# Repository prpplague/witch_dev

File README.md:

WITCH Development
=========

Repository for misc documents and code relating to the study of the Harwell
WITCH. The Harwell computer, later known as the Wolverhampton Instrument for
Teaching Computing from Harwell (WITCH), or the Harwell Dekatron Computer,
was an early British relay-based computer. It is currently being restored at
The National Museum of Computing at Bletchley Park, where it is described as
"the oldest original functioning electronic stored program computer in the 
world".

http://www.witch-e.org

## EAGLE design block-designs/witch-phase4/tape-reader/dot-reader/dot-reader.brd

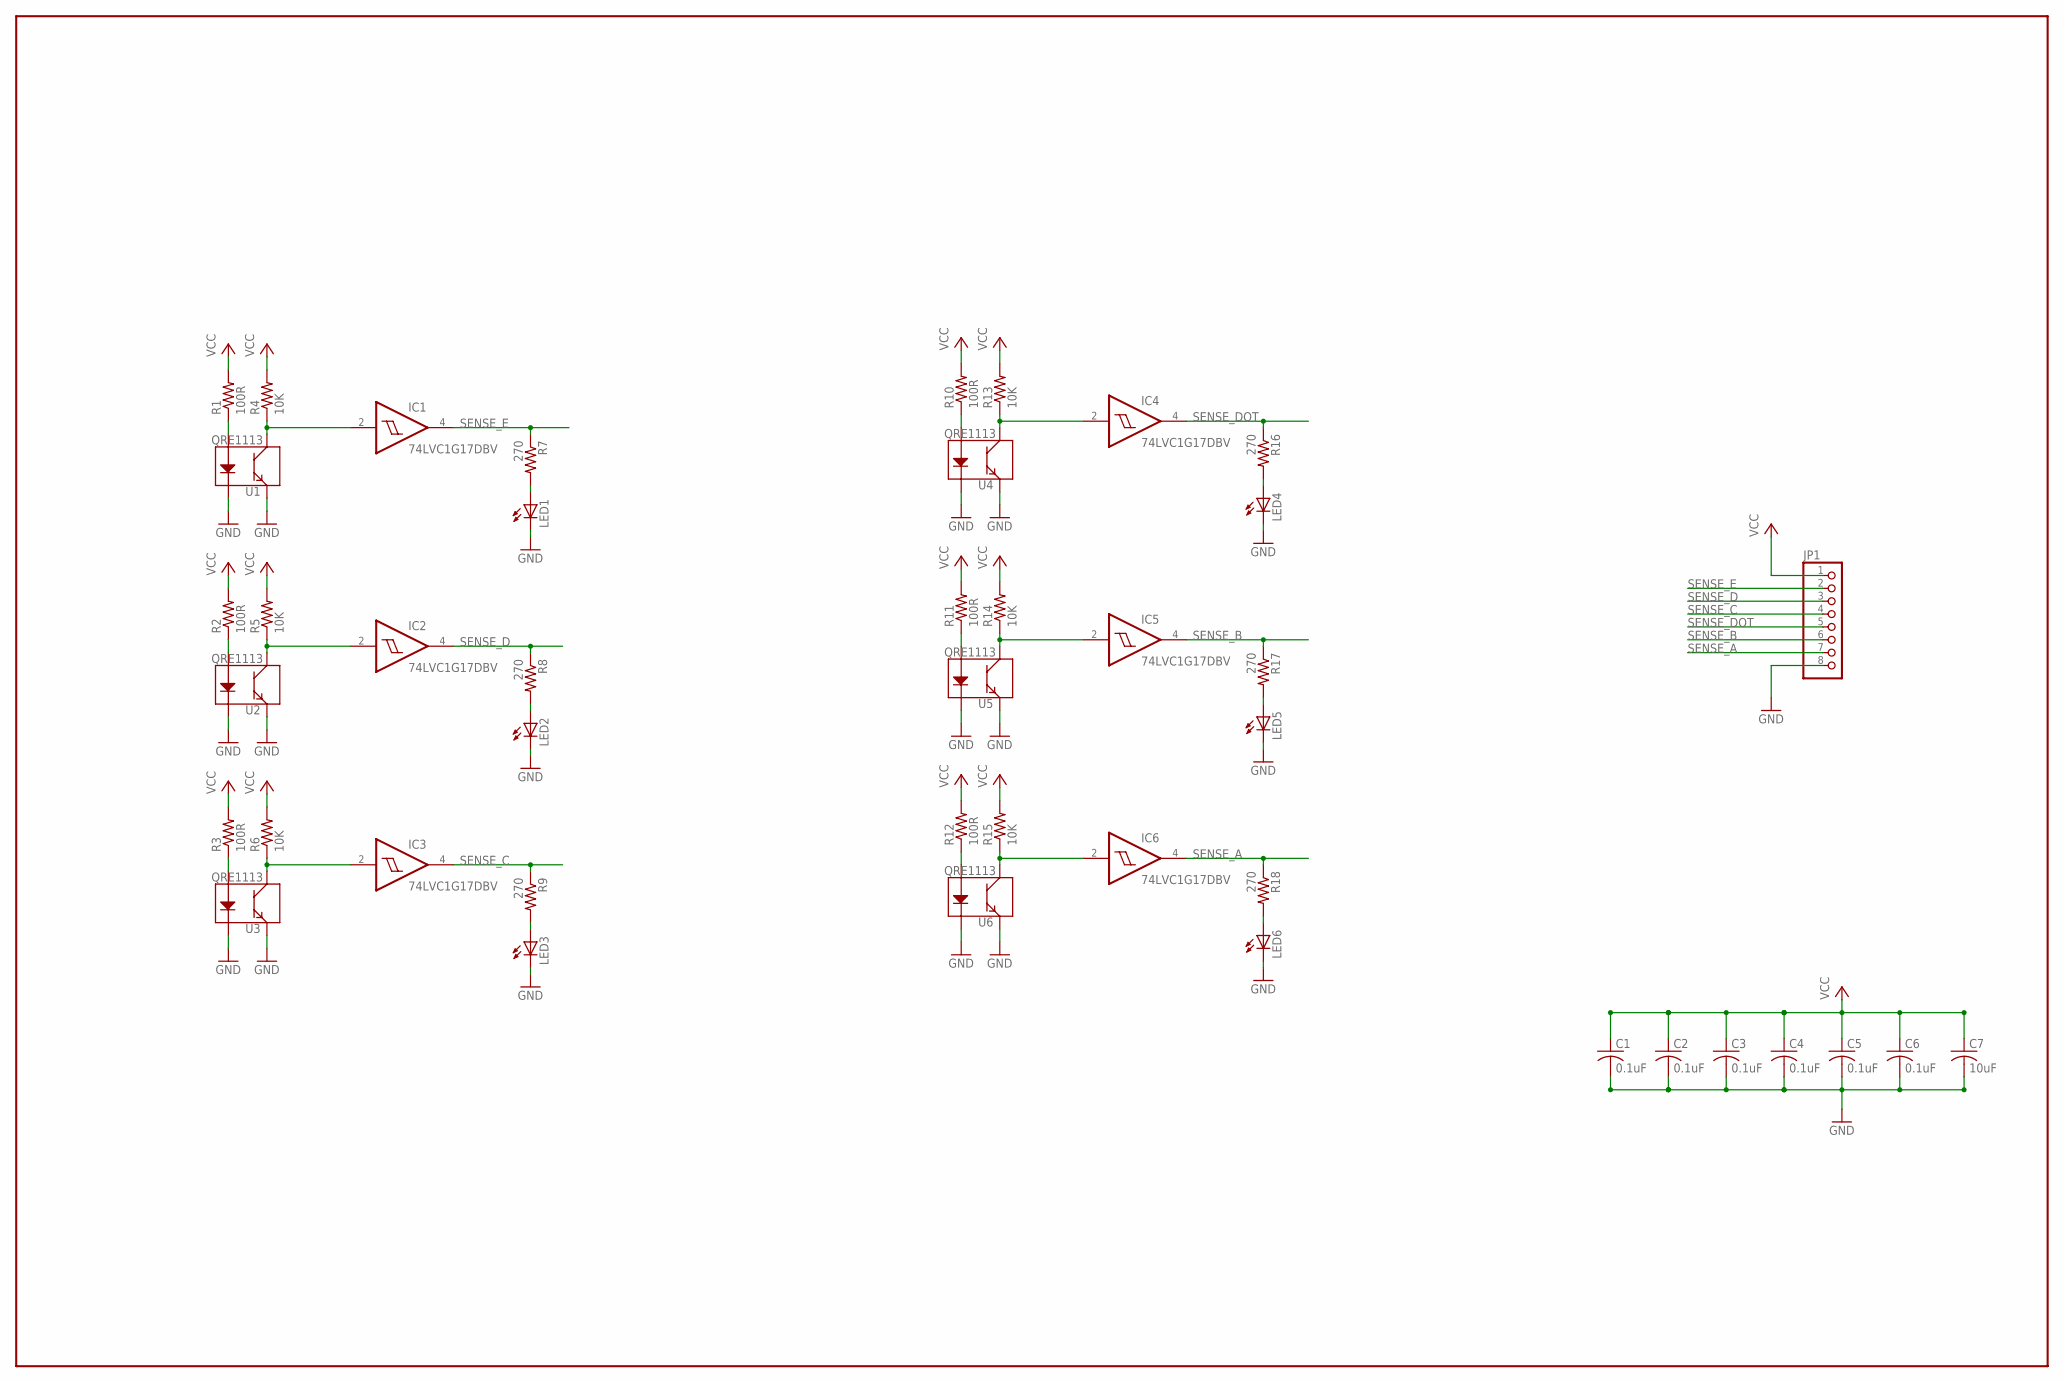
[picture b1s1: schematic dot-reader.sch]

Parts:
C1, C2, C3, C4, C5, C6: 0.1uF; C0603
C7: 10uF; C0805
IC1, IC2, IC3, IC4, IC5, IC6: 74LVC1G17DBV; SOT23-5
JP1: PINHD-1X8; 1X08
LED1, LED2, LED3, LED4, LED5, LED6: LEDCHIP-LED0805; CHIP-LED0805
R1, R2, R3, R10, R11, R12: 100R; M0805
R4, R5, R6, R13, R14, R15: 10K; M0805
R7, R8, R9, R16, R17, R18: 270; R0805
U1, U2, U3, U4, U5, U6: QRE1113

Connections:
A: IC1.2 (I), R4.1, U1.3 (C)
B: IC2.2 (I), R5.1, U2.3 (C)
C: IC4.2 (I), R13.1, U4.3 (C)
D: IC5.2 (I), R14.1, U5.3 (C)
DOT: IC3.2 (I), R6.1, U3.3 (C)
E: IC6.2 (I), R15.1, U6.3 (C)
GND: C1.2, C2.2, C3.2, C4.2, C5.2, C6.2, C7.2, IC1.3 (GND), IC2.3 (GND), IC3.3 (GND), IC4.3 (GND), IC5.3 (GND), IC6.3 (GND), JP1.8, LED1.C, LED2.C, LED3.C, LED4.C, LED5.C, LED6.C, U1.2 (K), U1.4 (E), U2.2 (K), U2.4 (E), U3.2 (K), U3.4 (E), U4.2 (K), U4.4 (E), U5.2 (K), U5.4 (E), U6.2 (K), U6.4 (E)
unnamed: R1.1, U1.1 (A)
unnamed: LED2.A, R8.2
unnamed: R2.1, U2.1 (A)
unnamed: LED4.A, R16.2
unnamed: R3.1, U3.1 (A)
unnamed: LED5.A, R17.2
unnamed: R10.1, U4.1 (A)
unnamed: LED3.A, R9.2
unnamed: R11.1, U5.1 (A)
unnamed: LED6.A, R18.2
unnamed: R12.1, U6.1 (A)
unnamed: LED1.A, R7.2
SENSE_A: IC6.4 (O), JP1.7, R18.1
SENSE_B: IC5.4 (O), JP1.6, R17.1
SENSE_C: IC3.4 (O), JP1.4, R9.1
SENSE_D: IC2.4 (O), JP1.3, R8.1
SENSE_DOT: IC4.4 (O), JP1.5, R16.1
SENSE_E: IC1.4 (O), JP1.2, R7.1
VCC: C1.1, C2.1, C3.1, C4.1, C5.1, C6.1, C7.1, IC1.5 (VCC), IC2.5 (VCC), IC3.5 (VCC), IC4.5 (VCC), IC5.5 (VCC), IC6.5 (VCC), JP1.1, R1.2, R2.2, R3.2, R4.2, R5.2, R6.2, R10.2, R11.2, R12.2, R13.2, R14.2, R15.2

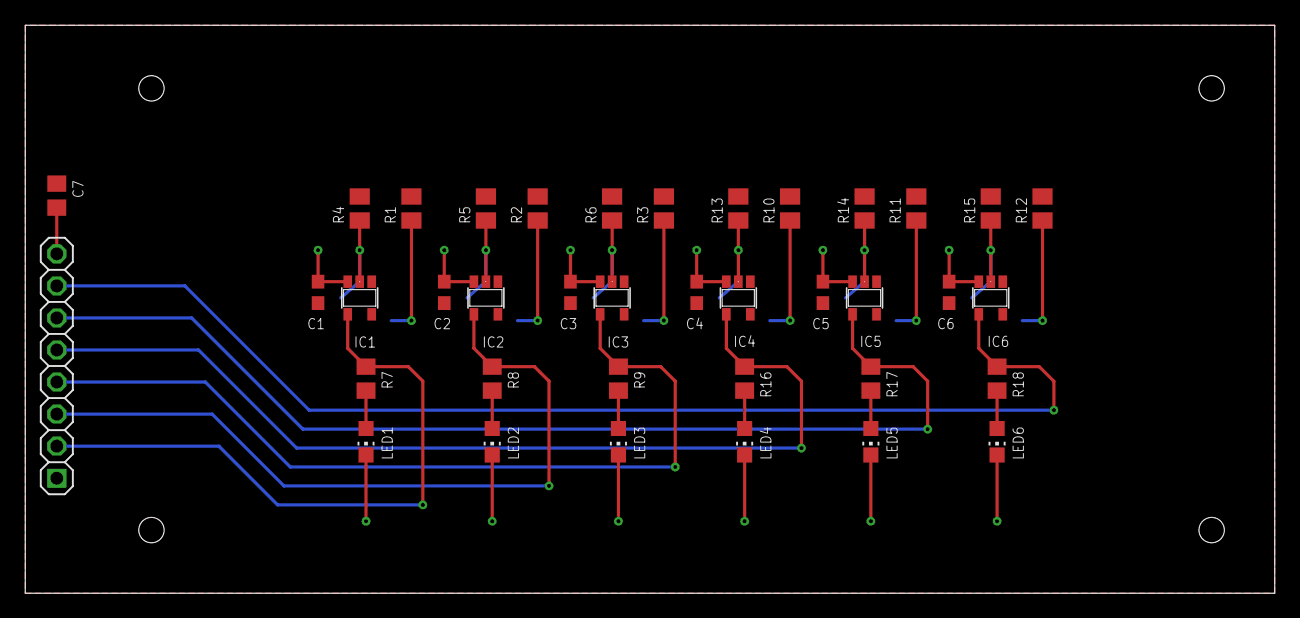
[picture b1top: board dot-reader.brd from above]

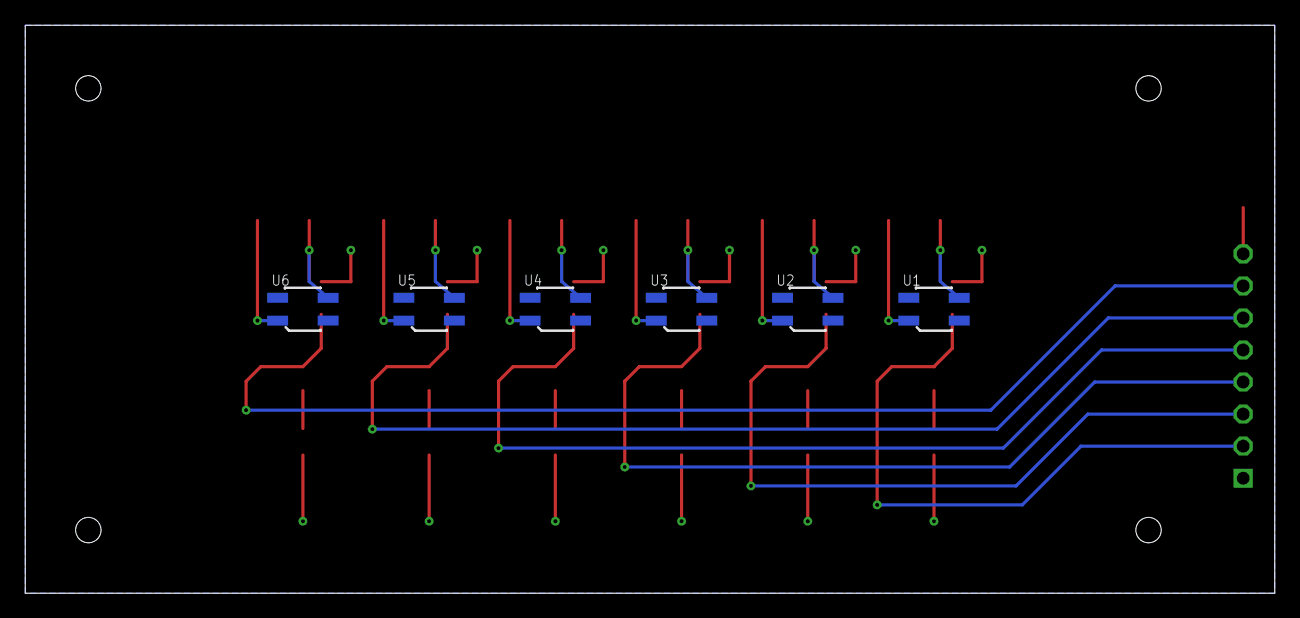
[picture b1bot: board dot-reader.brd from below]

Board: 2 copper layers, 99.0 x 45.0 mm, 44 parts (6 on the bottom side), 26 nets.

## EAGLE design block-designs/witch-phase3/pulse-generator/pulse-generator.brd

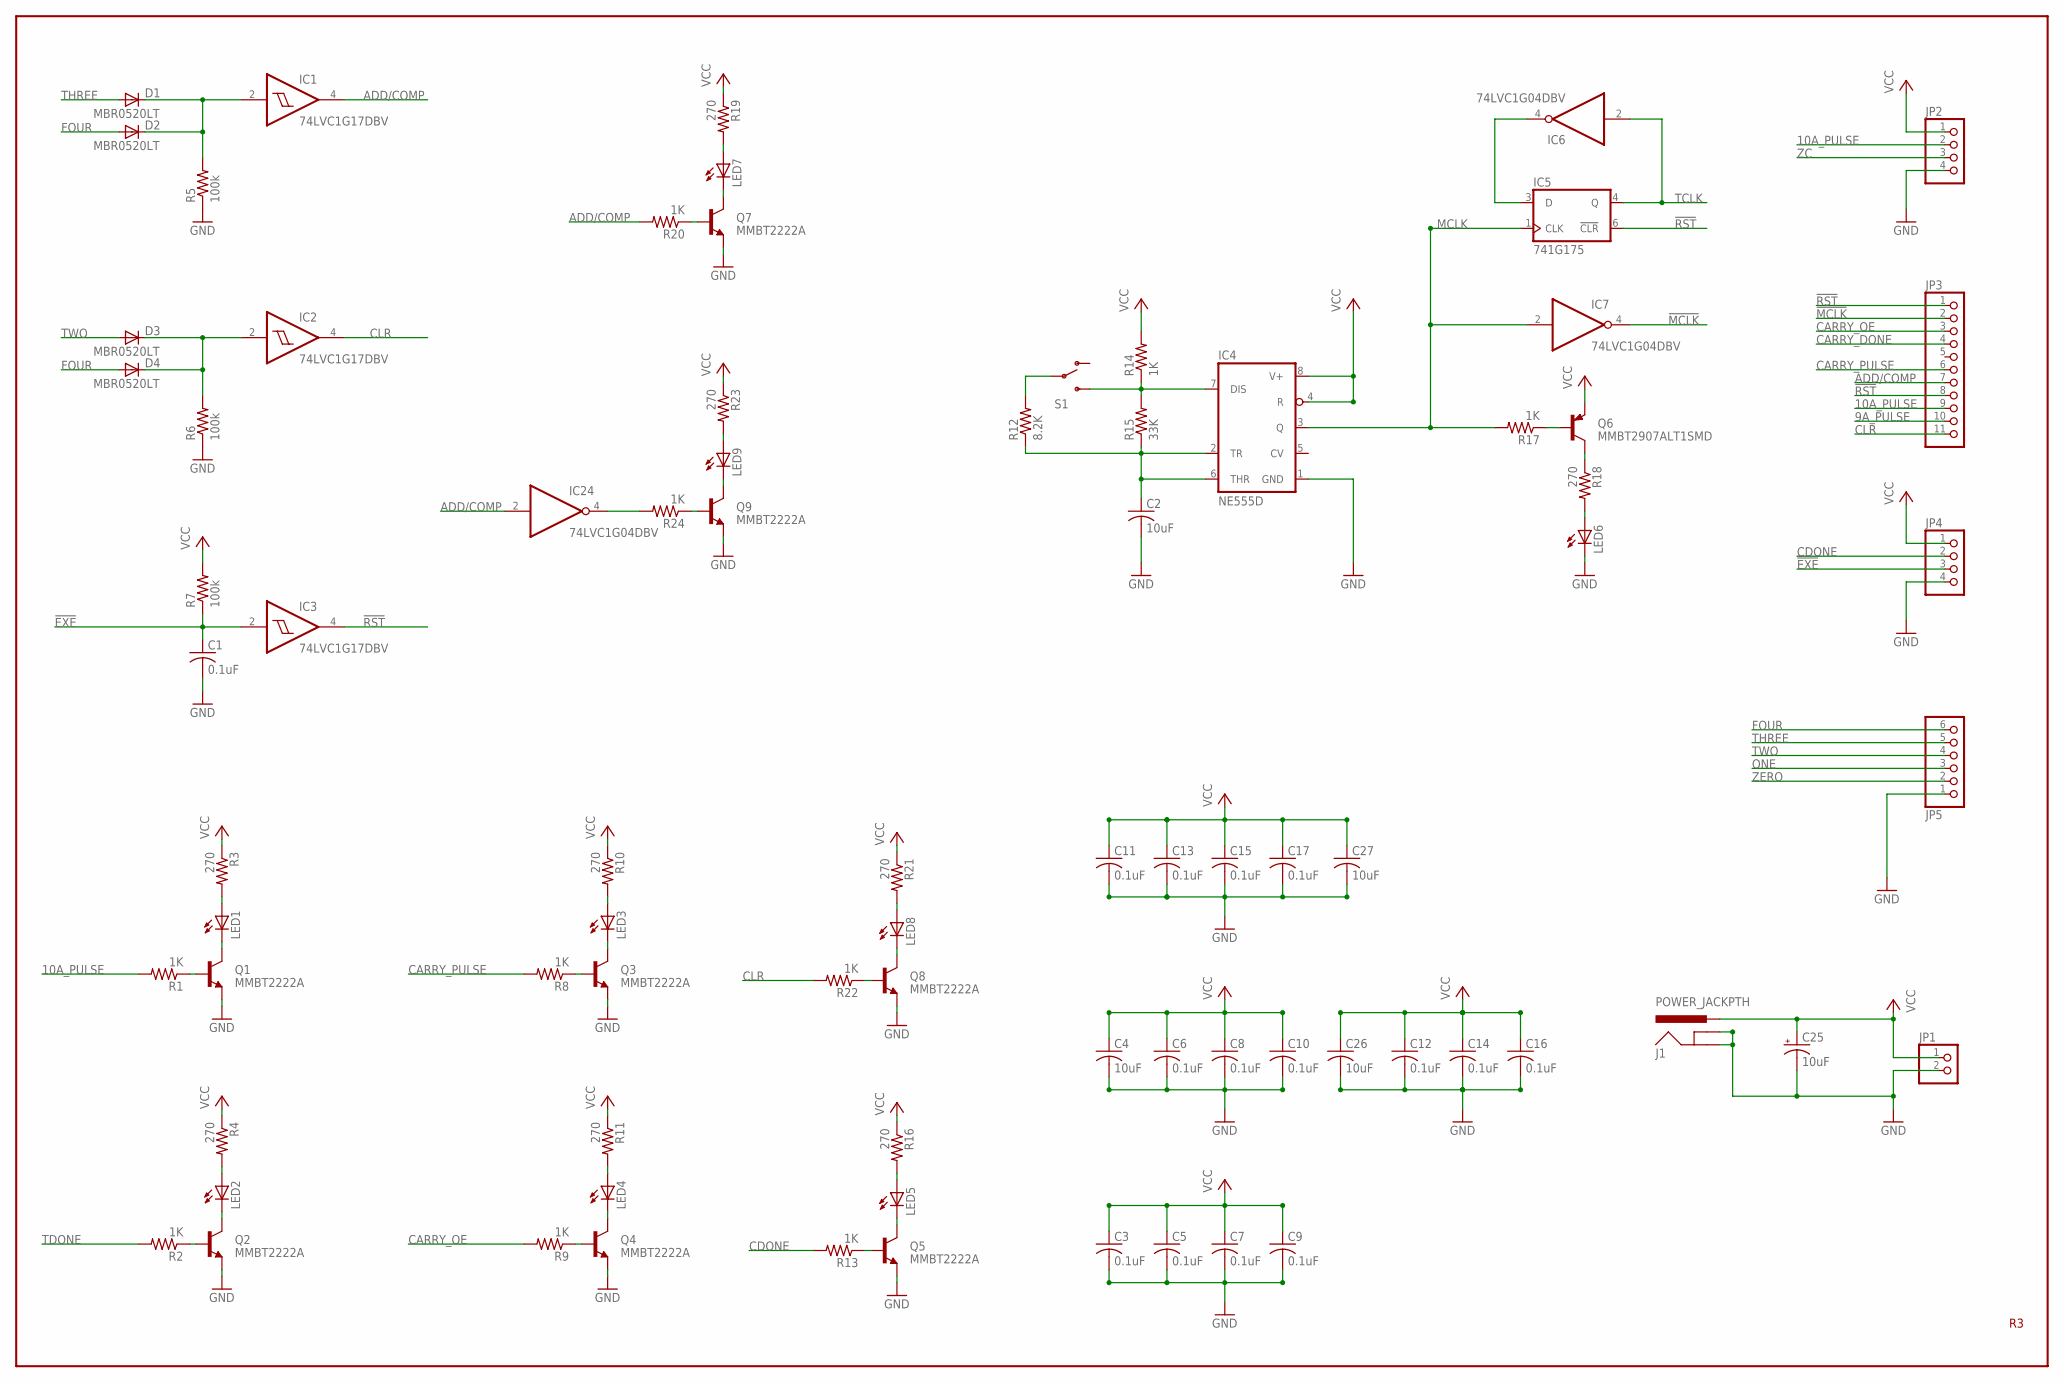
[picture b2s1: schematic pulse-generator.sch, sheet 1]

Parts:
C1, C7: 0.1uF; C0805
C2, C4, C26, C27: 10uF; C0805
C3, C5, C6, C8, C9, C10, C11, C12, C13, C14, C15, C16, C17: 0.1uF; C0603
C25: 10uF; EIA3216
D1, D2, D3, D4: MBR0520LT; SOD123
IC1, IC2, IC3: 74LVC1G17DBV; SOT23-5
IC4: NE555D; SO08
IC5: 741G175; DBV_R-PDSO-G6
IC6, IC7, IC24: 74LVC1G04DBV; SOT23-5
J1: POWER_JACKPTH; POWER_JACK_PTH
JP1: PINHD-1X2; 1X02
JP2, JP4: PINHD-1X4; 1X04
JP3: PINHD-1X11; 1X11
JP5: PINHD-1X6; 1X06
LED1, LED2, LED3, LED4, LED5, LED6, LED7, LED8, LED9: LEDCHIP-LED0805; CHIP-LED0805
Q1, Q2, Q3, Q4, Q5, Q7, Q8, Q9: MMBT2222A; SOT23-3
Q6: MMBT2907ALT1SMD; SOT23-BEC
R1, R2, R8, R9, R13, R14, R17, R20, R22, R24: 1K; R0805
R3, R4, R10, R11, R16, R18, R19, R21, R23: 270; R0805
R5, R6, R7: 100k; R0805
R12: 8.2K; R0805
R15: 33K; R0805
S1: SWITCH-SPDTPTH; SWITCH-SPDT

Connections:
9A_PULSE: JP3.10; also elsewhere on the board
10A_PULSE: JP2.2, JP3.9, R1.2; also elsewhere on the board
!EXE: C1.1, IC3.2 (I), JP4.3, R7.1
!MCLK: IC7.4 (O), JP3.2; also elsewhere on the board
!RST: IC3.4 (O), IC5.6 (!CLR), JP3.1, JP3.8; also elsewhere on the board
ADD/COMP: IC1.4 (O), IC24.2 (I), JP3.7, R20.2
CARRY_DONE: JP3.4; also elsewhere on the board
CARRY_OE: JP3.3, R9.2; also elsewhere on the board
CARRY_PULSE: JP3.6, R8.2; also elsewhere on the board
CDONE: JP4.2, R13.2; also elsewhere on the board
CLR: IC2.4 (O), JP3.11, R22.2
FOUR: D2.A, D4.A, JP5.6
GND: C1.2, C2.2, C3.2, C4.2, C5.2, C6.2, C7.2, C8.2, C9.2, C10.2, C11.2, C12.2, C13.2, C14.2, C15.2, C16.2, C17.2, C25.C (-), C26.2, C27.2, IC1.3 (GND), IC2.3 (GND), IC3.3 (GND), IC4.1 (GND), IC5.2 (GND), IC6.3 (GND), IC7.3 (GND), IC24.3 (GND), J1.GND, J1.GNDBREAK, JP1.2, JP2.4, JP4.4, JP5.1, LED6.C, Q1.2 (E), Q2.2 (E), Q3.2 (E), Q4.2 (E), Q5.2 (E), Q7.2 (E), Q8.2 (E), Q9.2 (E), R5.1, R6.1; also elsewhere on the board
MCLK: IC4.3 (Q), IC5.1 (CLK), IC7.2 (I), R17.2
unnamed: IC5.3 (D), IC6.4 (O)
unnamed: C2.1, IC4.2 (TR), IC4.6 (THR), R12.1, R15.1
unnamed: IC4.7 (DIS), R14.1, R15.2, S1.3 (S)
unnamed: R12.2, S1.2
unnamed: Q6.B, R17.1
unnamed: Q6.C, R18.1
unnamed: LED6.A, R18.2
unnamed: LED3.C, Q3.3 (C)
unnamed: LED7.C, Q7.3 (C)
unnamed: LED1.C, Q1.3 (C)
unnamed: Q7.1 (B), R20.1
unnamed: D1.C, D2.C, IC1.2 (I), R5.2
unnamed: D3.C, D4.C, IC2.2 (I), R6.2
unnamed: LED7.A, R19.2
unnamed: LED8.C, Q8.3 (C)
unnamed: Q8.1 (B), R22.1
unnamed: Q3.1 (B), R8.1
unnamed: LED3.A, R10.2
unnamed: Q1.1 (B), R1.1
unnamed: LED8.A, R21.2
unnamed: LED1.A, R3.2
unnamed: LED9.C, Q9.3 (C)
unnamed: Q9.1 (B), R24.1
unnamed: LED2.C, Q2.3 (C)
unnamed: Q2.1 (B), R2.1
unnamed: LED2.A, R4.2
unnamed: LED4.C, Q4.3 (C)
unnamed: Q4.1 (B), R9.1
unnamed: LED4.A, R11.2
unnamed: LED5.C, Q5.3 (C)
unnamed: Q5.1 (B), R13.1
unnamed: LED5.A, R16.2
unnamed: LED9.A, R23.2
unnamed: IC24.4 (O), R24.2
ONE: JP5.3
TCLK: IC5.4 (Q), IC6.2 (I); also elsewhere on the board
TDONE: R2.2; also elsewhere on the board
THREE: D1.A, JP5.5
TWO: D3.A, JP5.4
VCC: C3.1, C4.1, C5.1, C6.1, C7.1, C8.1, C9.1, C10.1, C11.1, C12.1, C13.1, C14.1, C15.1, C16.1, C17.1, C25.A (+), C26.1, C27.1, IC1.5 (VCC), IC2.5 (VCC), IC3.5 (VCC), IC4.4 (R), IC4.8 (V+), IC5.5 (VCC), IC6.5 (VCC), IC7.5 (VCC), IC24.5 (VCC), J1.PWR, JP1.1, JP2.1, JP4.1, Q6.E, R3.1, R4.1, R7.2, R10.1, R11.1, R14.2, R16.1, R19.1, R21.1, R23.1; also elsewhere on the board
ZC: JP2.3; also elsewhere on the board
ZERO: JP5.2

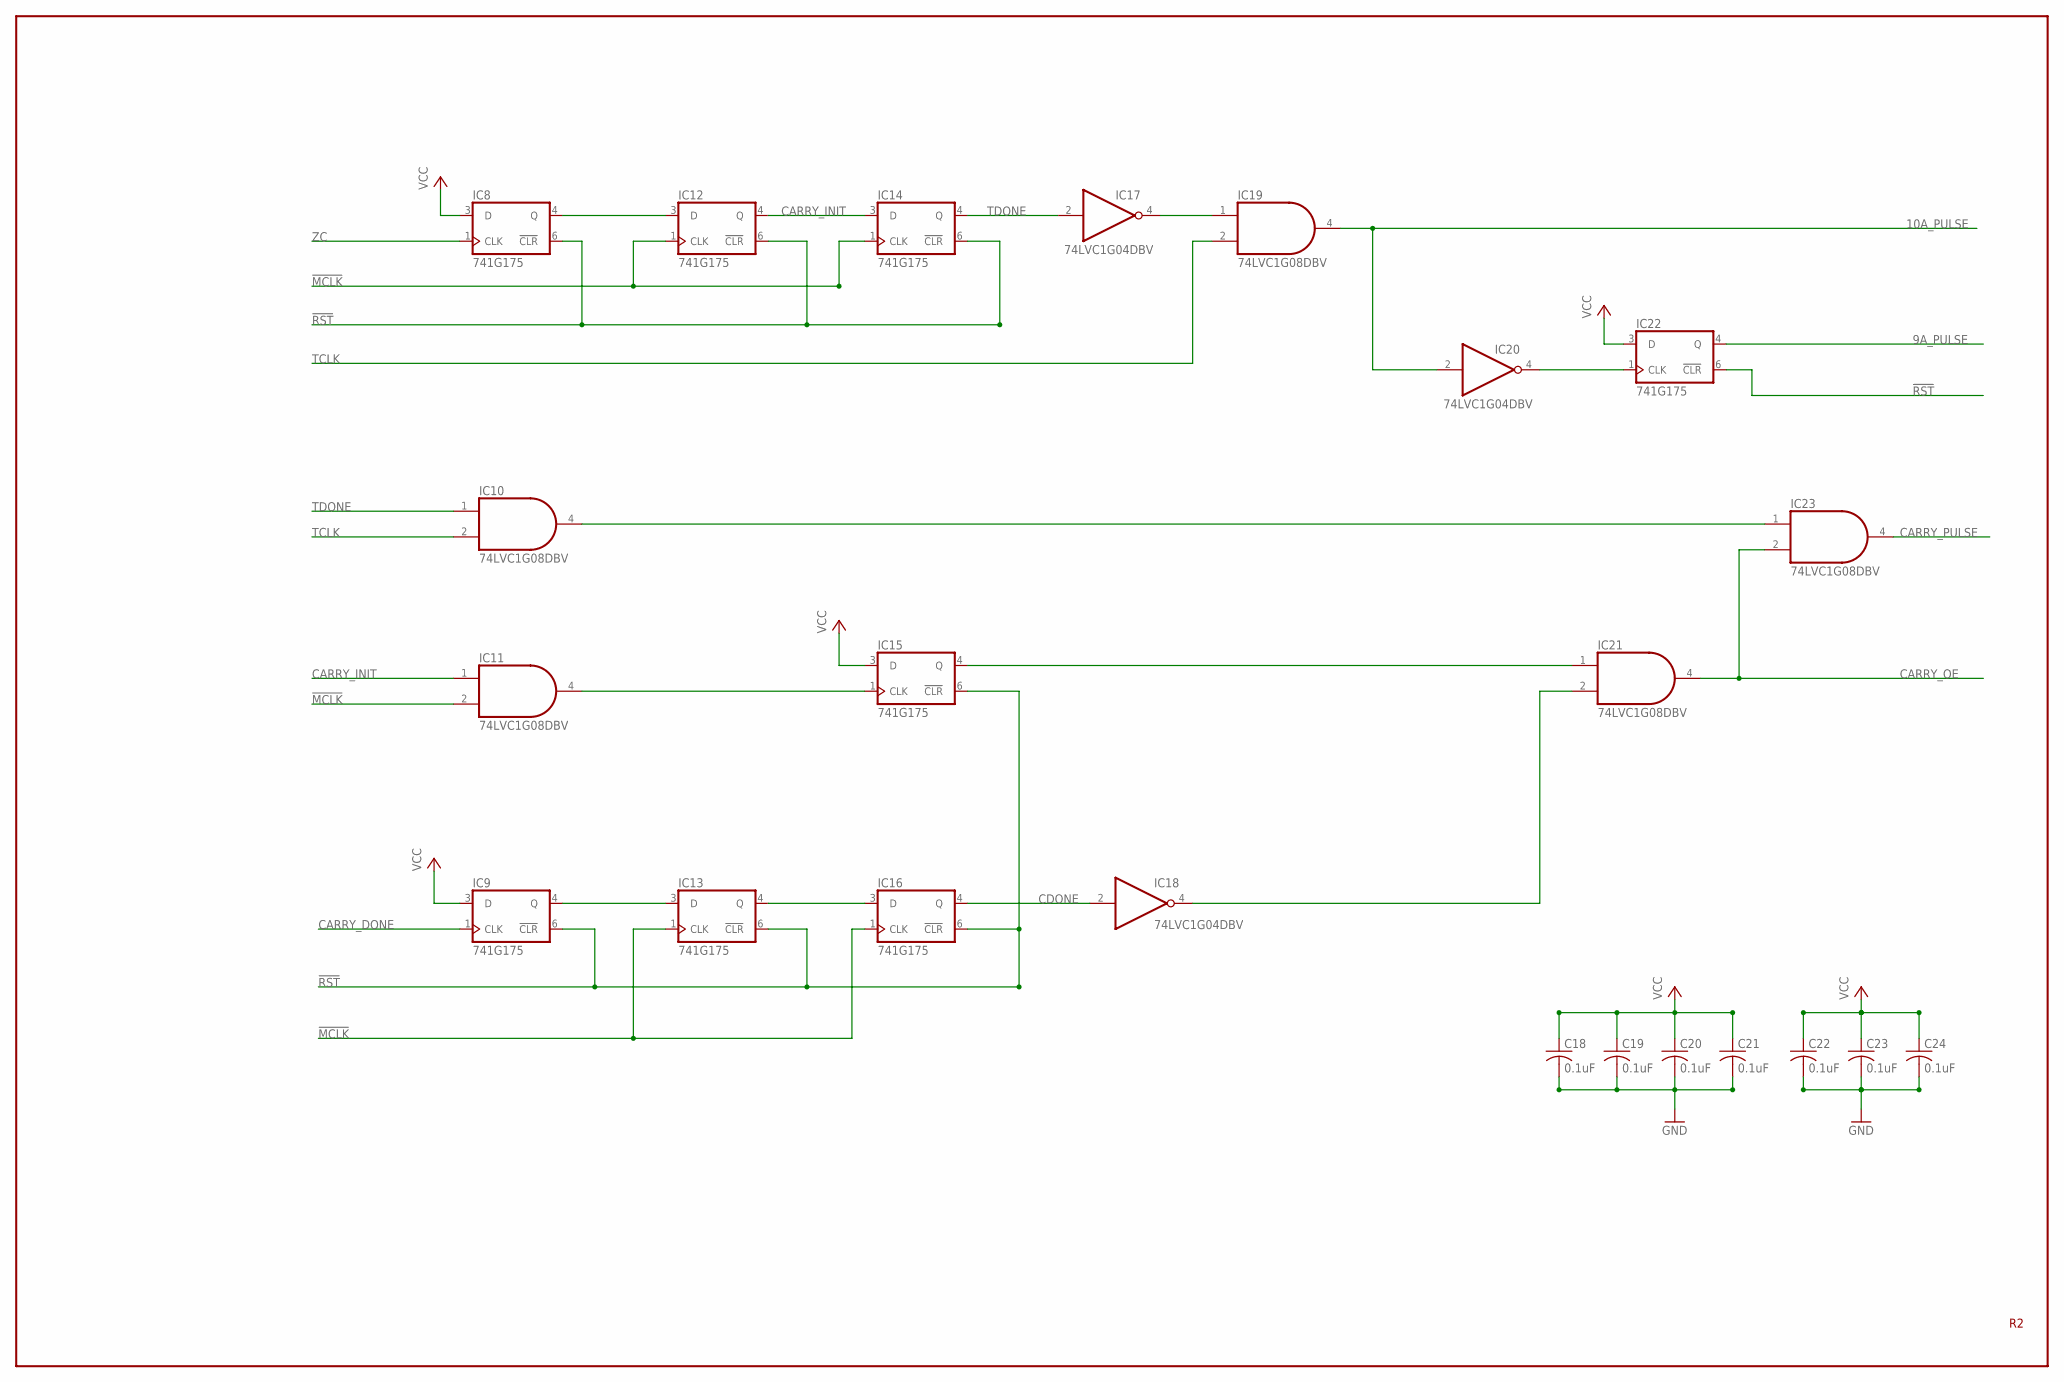
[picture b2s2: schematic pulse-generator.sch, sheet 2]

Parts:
C18, C19, C20, C21, C22, C23, C24: 0.1uF; C0603
IC8, IC9, IC12, IC13, IC14, IC15, IC16, IC22: 741G175; DBV_R-PDSO-G6
IC10, IC11, IC19, IC21, IC23: 74LVC1G08DBV; SOT23-5
IC17, IC18, IC20: 74LVC1G04DBV; SOT23-5

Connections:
9A_PULSE: IC22.4 (Q); also elsewhere on the board
10A_PULSE: IC19.4 (O), IC20.2 (I); also elsewhere on the board
!CDONE: IC18.4 (O), IC21.2 (I1)
!MCLK: IC11.2 (I1), IC12.1 (CLK), IC13.1 (CLK), IC14.1 (CLK), IC16.1 (CLK); also elsewhere on the board
!RST: IC8.6 (!CLR), IC9.6 (!CLR), IC12.6 (!CLR), IC13.6 (!CLR), IC14.6 (!CLR), IC15.6 (!CLR), IC16.6 (!CLR), IC22.6 (!CLR); also elsewhere on the board
!TDONE: IC17.4 (O), IC19.1 (I0)
CARRY_DONE: IC9.1 (CLK); also elsewhere on the board
CARRY_INIT: IC11.1 (I0), IC12.4 (Q), IC14.3 (D)
CARRY_OE: IC21.4 (O), IC23.2 (I1); also elsewhere on the board
CARRY_PULSE: IC23.4 (O); also elsewhere on the board
CDONE: IC16.4 (Q), IC18.2 (I); also elsewhere on the board
GND: C18.2, C19.2, C20.2, C21.2, C22.2, C23.2, C24.2, IC8.2 (GND), IC9.2 (GND), IC10.3 (GND), IC11.3 (GND), IC12.2 (GND), IC13.2 (GND), IC14.2 (GND), IC15.2 (GND), IC16.2 (GND), IC17.3 (GND), IC18.3 (GND), IC19.3 (GND), IC20.3 (GND), IC21.3 (GND), IC22.2 (GND), IC23.3 (GND); also elsewhere on the board
unnamed: IC8.4 (Q), IC12.3 (D)
unnamed: IC10.4 (O), IC23.1 (I0)
unnamed: IC9.4 (Q), IC13.3 (D)
unnamed: IC15.4 (Q), IC21.1 (I0)
unnamed: IC11.4 (O), IC15.1 (CLK)
unnamed: IC13.4 (Q), IC16.3 (D)
unnamed: IC20.4 (O), IC22.1 (CLK)
TCLK: IC10.2 (I1), IC19.2 (I1); also elsewhere on the board
TDONE: IC10.1 (I0), IC14.4 (Q), IC17.2 (I); also elsewhere on the board
VCC: C18.1, C19.1, C20.1, C21.1, C22.1, C23.1, C24.1, IC8.3 (D), IC8.5 (VCC), IC9.3 (D), IC9.5 (VCC), IC10.5 (VCC), IC11.5 (VCC), IC12.5 (VCC), IC13.5 (VCC), IC14.5 (VCC), IC15.3 (D), IC15.5 (VCC), IC16.5 (VCC), IC17.5 (VCC), IC18.5 (VCC), IC19.5 (VCC), IC20.5 (VCC), IC21.5 (VCC), IC22.3 (D), IC22.5 (VCC), IC23.5 (VCC); also elsewhere on the board
ZC: IC8.1 (CLK); also elsewhere on the board

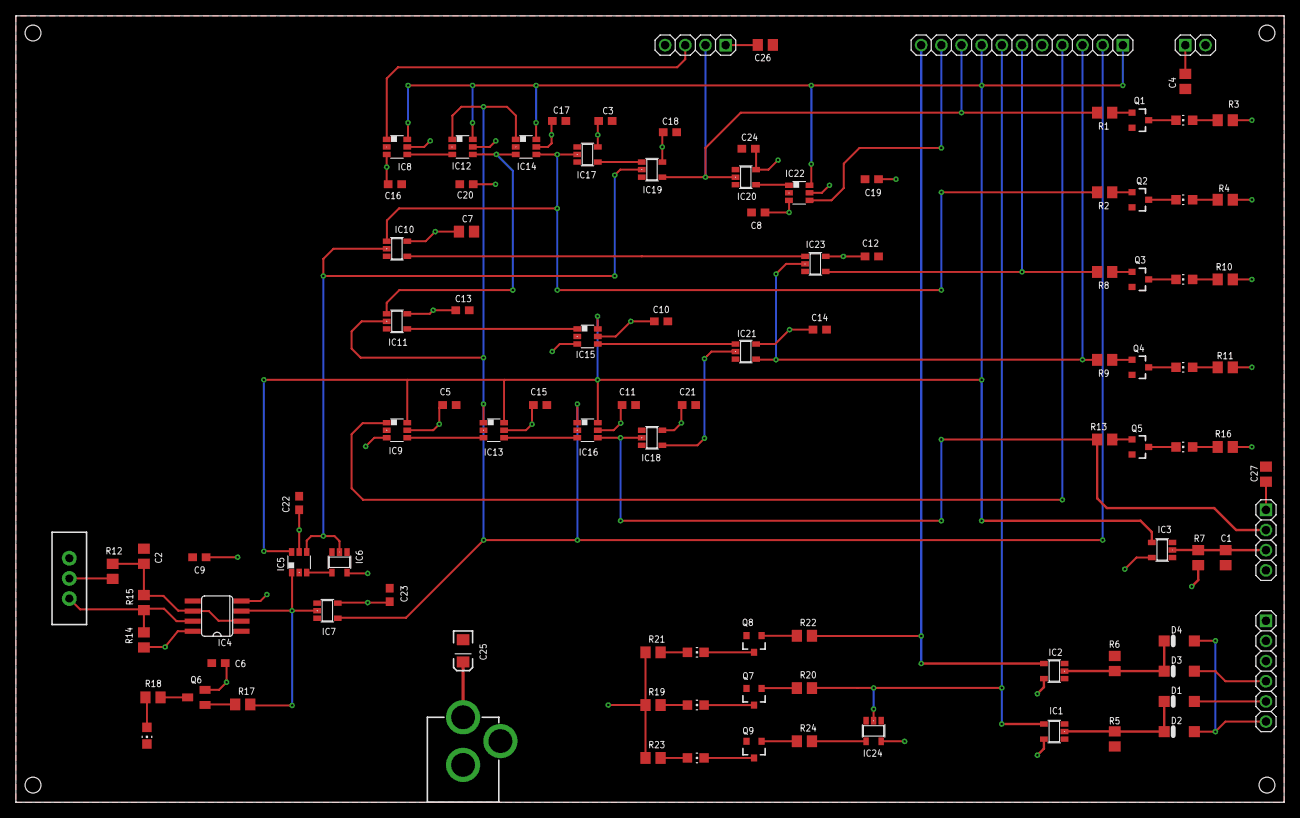
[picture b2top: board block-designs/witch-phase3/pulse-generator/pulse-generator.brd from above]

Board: 2 copper layers, 159.8 x 99.1 mm, 104 parts (0 on the bottom side), 64 nets.

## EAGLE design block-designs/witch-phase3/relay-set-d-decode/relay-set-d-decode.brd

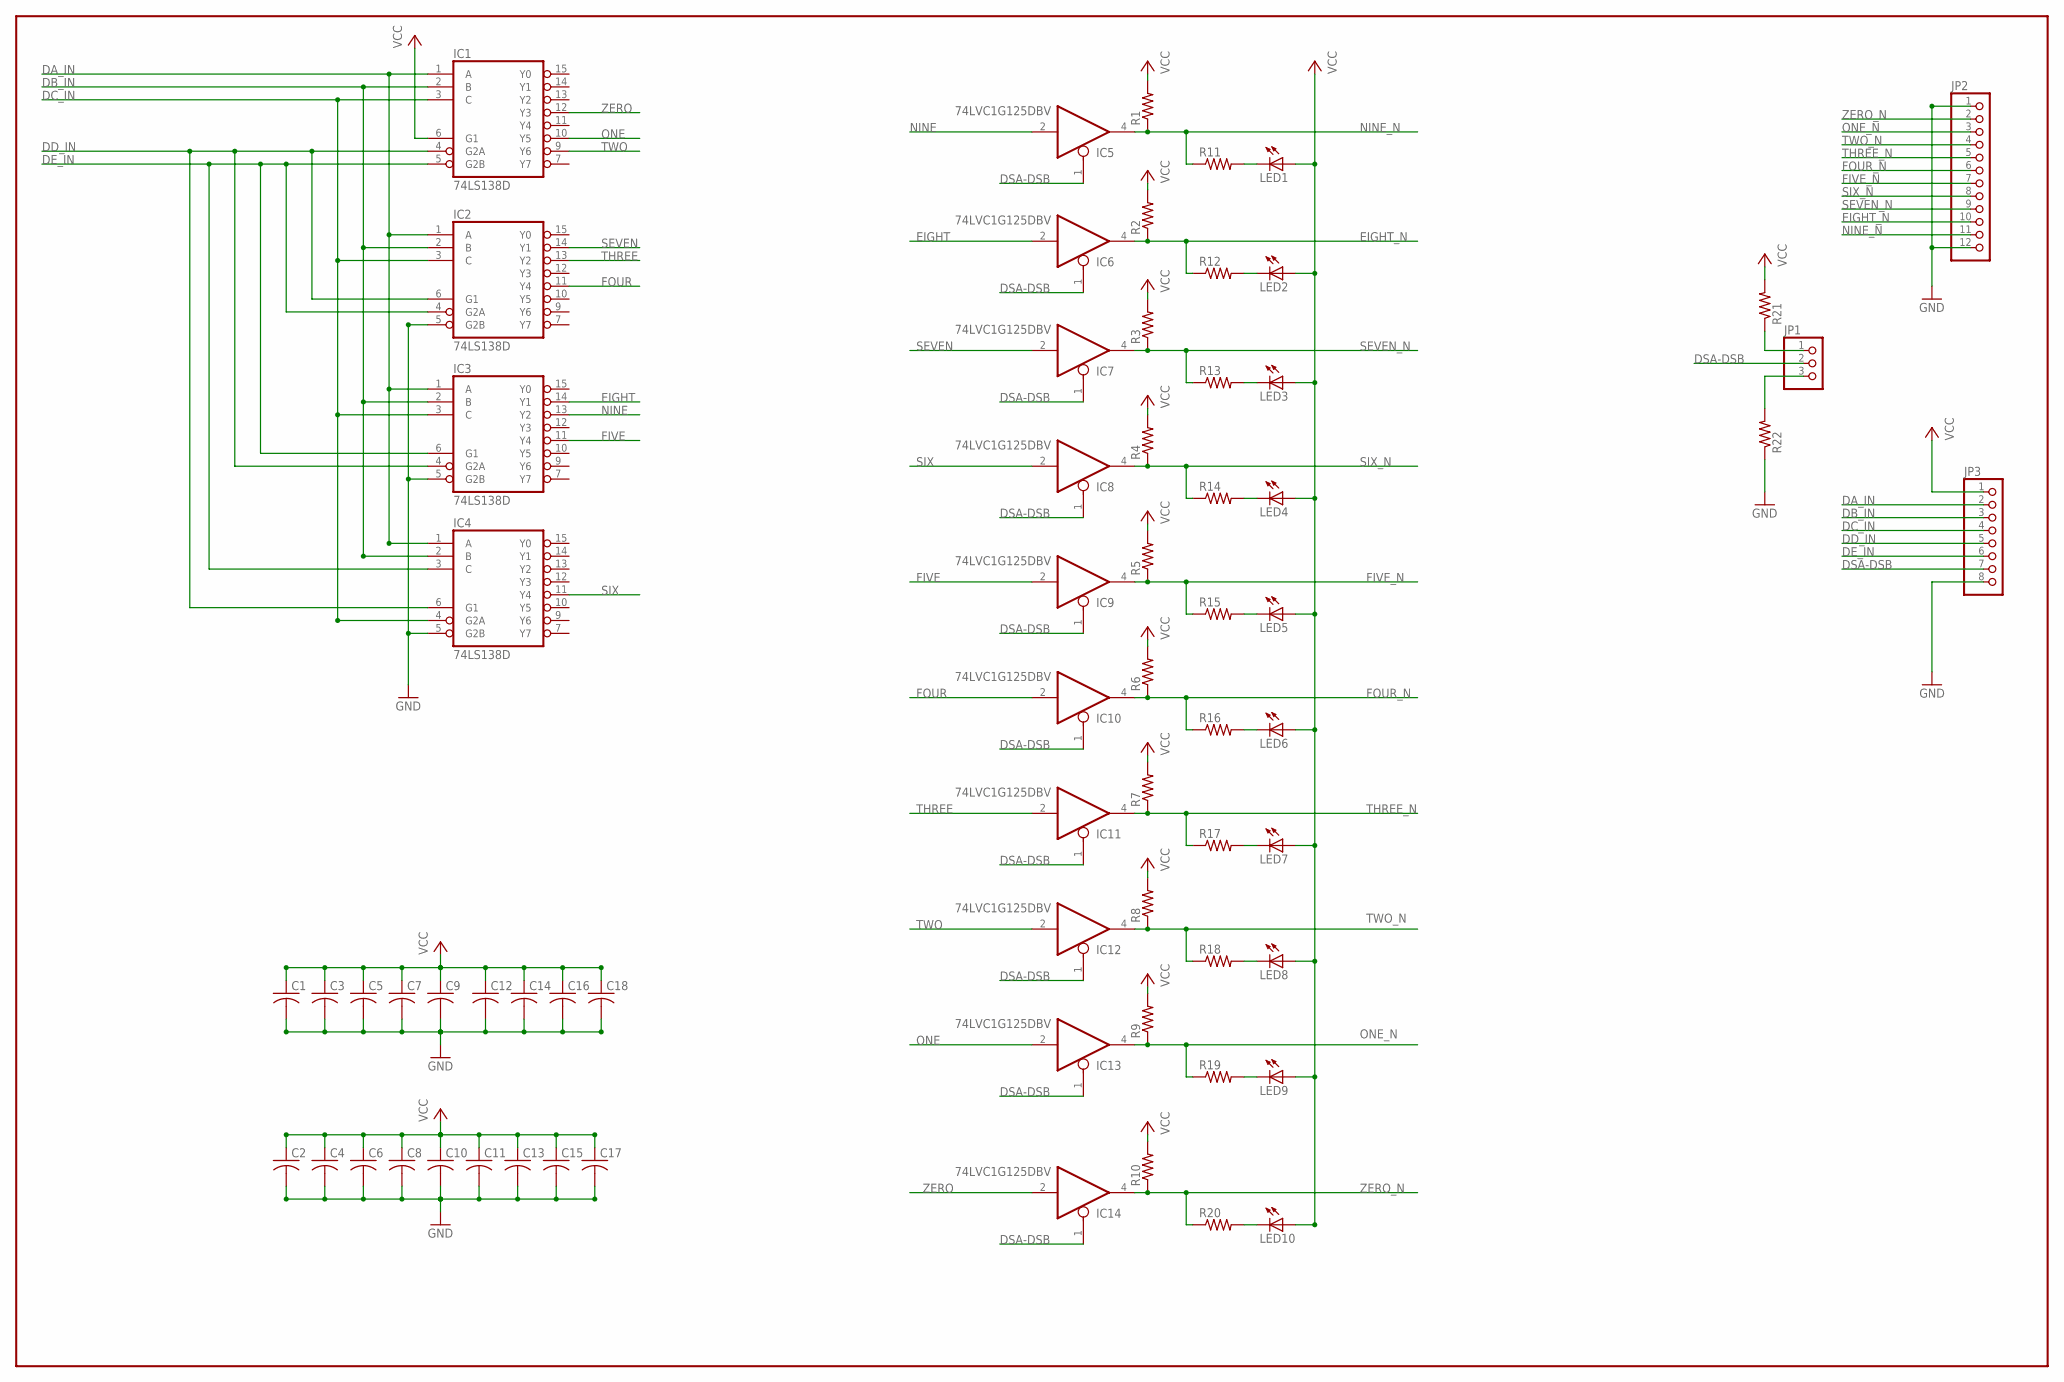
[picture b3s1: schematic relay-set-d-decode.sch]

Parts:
C1, C2, C3, C4, C6, C8, C10, C11, C12, C13, C14, C15, C16, C17, C18: C-USC0603; C0603
C5, C7, C9: C-USC0805; C0805
IC1, IC2, IC3, IC4: 74LS138D; SO16
IC5, IC6, IC7, IC8, IC9, IC10, IC11, IC12, IC13, IC14: 74LVC1G125DBV; SOT23-5
JP1: PINHD-1X3; 1X03
JP2: PINHD-1X12; 1X12
JP3: PINHD-1X8; 1X08
LED1, LED2, LED3, LED4, LED5, LED6, LED7, LED8, LED9, LED10: LEDCHIP-LED0805; CHIP-LED0805
R1, R2, R3, R4, R5, R6, R7, R8, R9, R10, R11, R12, R13, R14, R15, R16, R17, R18, R19, R20, R21, R22: R-US_R0805; R0805

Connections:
DA_IN: IC1.1 (A), IC2.1 (A), IC3.1 (A), IC4.1 (A), JP3.2
DB_IN: IC1.2 (B), IC2.2 (B), IC3.2 (B), IC4.2 (B), JP3.3
DC_IN: IC1.3 (C), IC2.3 (C), IC3.3 (C), IC4.4 (G2A), JP3.4
DD_IN: IC1.4 (G2A), IC2.6 (G1), IC3.4 (G2A), IC4.6 (G1), JP3.5
DE_IN: IC1.5 (G2B), IC2.4 (G2A), IC3.6 (G1), IC4.3 (C), JP3.6
DSA-DSB: IC5.1 (OE), IC6.1 (OE), IC7.1 (OE), IC8.1 (OE), IC9.1 (OE), IC10.1 (OE), IC11.1 (OE), IC12.1 (OE), IC13.1 (OE), IC14.1 (OE), JP1.2, JP3.7
EIGHT: IC3.14 (Y1), IC6.2 (I)
EIGHT_N: IC6.4 (O), JP2.10, R2.1, R12.1
FIVE: IC3.11 (Y4), IC9.2 (I)
FIVE_N: IC9.4 (O), JP2.7, R5.1, R15.1
FOUR: IC2.11 (Y4), IC10.2 (I)
FOUR_N: IC10.4 (O), JP2.6, R6.1, R16.1
GND: C1.2, C2.2, C3.2, C4.2, C5.2, C6.2, C7.2, C8.2, C9.2, C10.2, C11.2, C12.2, C13.2, C14.2, C15.2, C16.2, C17.2, C18.2, IC1.8 (GND), IC2.5 (G2B), IC2.8 (GND), IC3.5 (G2B), IC3.8 (GND), IC4.5 (G2B), IC4.8 (GND), IC5.3 (GND), IC6.3 (GND), IC7.3 (GND), IC8.3 (GND), IC9.3 (GND), IC10.3 (GND), IC11.3 (GND), IC12.3 (GND), IC13.3 (GND), IC14.3 (GND), JP2.1, JP2.12, JP3.8, R22.1
unnamed: LED1.C, R11.2
unnamed: LED2.C, R12.2
unnamed: LED3.C, R13.2
unnamed: LED4.C, R14.2
unnamed: LED5.C, R15.2
unnamed: LED6.C, R16.2
unnamed: LED7.C, R17.2
unnamed: LED8.C, R18.2
unnamed: LED9.C, R19.2
unnamed: LED10.C, R20.2
unnamed: JP1.1, R21.1
unnamed: JP1.3, R22.2
NINE: IC3.13 (Y2), IC5.2 (I)
NINE_N: IC5.4 (O), JP2.11, R1.1, R11.1
ONE: IC1.10 (Y5), IC13.2 (I)
ONE_N: IC13.4 (O), JP2.3, R9.1, R19.1
SEVEN: IC2.14 (Y1), IC7.2 (I)
SEVEN_N: IC7.4 (O), JP2.9, R3.1, R13.1
SIX: IC4.11 (Y4), IC8.2 (I)
SIX_N: IC8.4 (O), JP2.8, R4.1, R14.1
THREE: IC2.13 (Y2), IC11.2 (I)
THREE_N: IC11.4 (O), JP2.5, R7.1, R17.1
TWO: IC1.9 (Y6), IC12.2 (I)
TWO_N: IC12.4 (O), JP2.4, R8.1, R18.1
VCC: C1.1, C2.1, C3.1, C4.1, C5.1, C6.1, C7.1, C8.1, C9.1, C10.1, C11.1, C12.1, C13.1, C14.1, C15.1, C16.1, C17.1, C18.1, IC1.6 (G1), IC1.16 (VCC), IC2.16 (VCC), IC3.16 (VCC), IC4.16 (VCC), IC5.5 (VCC), IC6.5 (VCC), IC7.5 (VCC), IC8.5 (VCC), IC9.5 (VCC), IC10.5 (VCC), IC11.5 (VCC), IC12.5 (VCC), IC13.5 (VCC), IC14.5 (VCC), JP3.1, LED1.A, LED2.A, LED3.A, LED4.A, LED5.A, LED6.A, LED7.A, LED8.A, LED9.A, LED10.A, R1.2, R2.2, R3.2, R4.2, R5.2, R6.2, R7.2, R8.2, R9.2, R10.2, R21.2
ZERO: IC1.12 (Y3), IC14.2 (I)
ZERO_N: IC14.4 (O), JP2.2, R10.1, R20.1

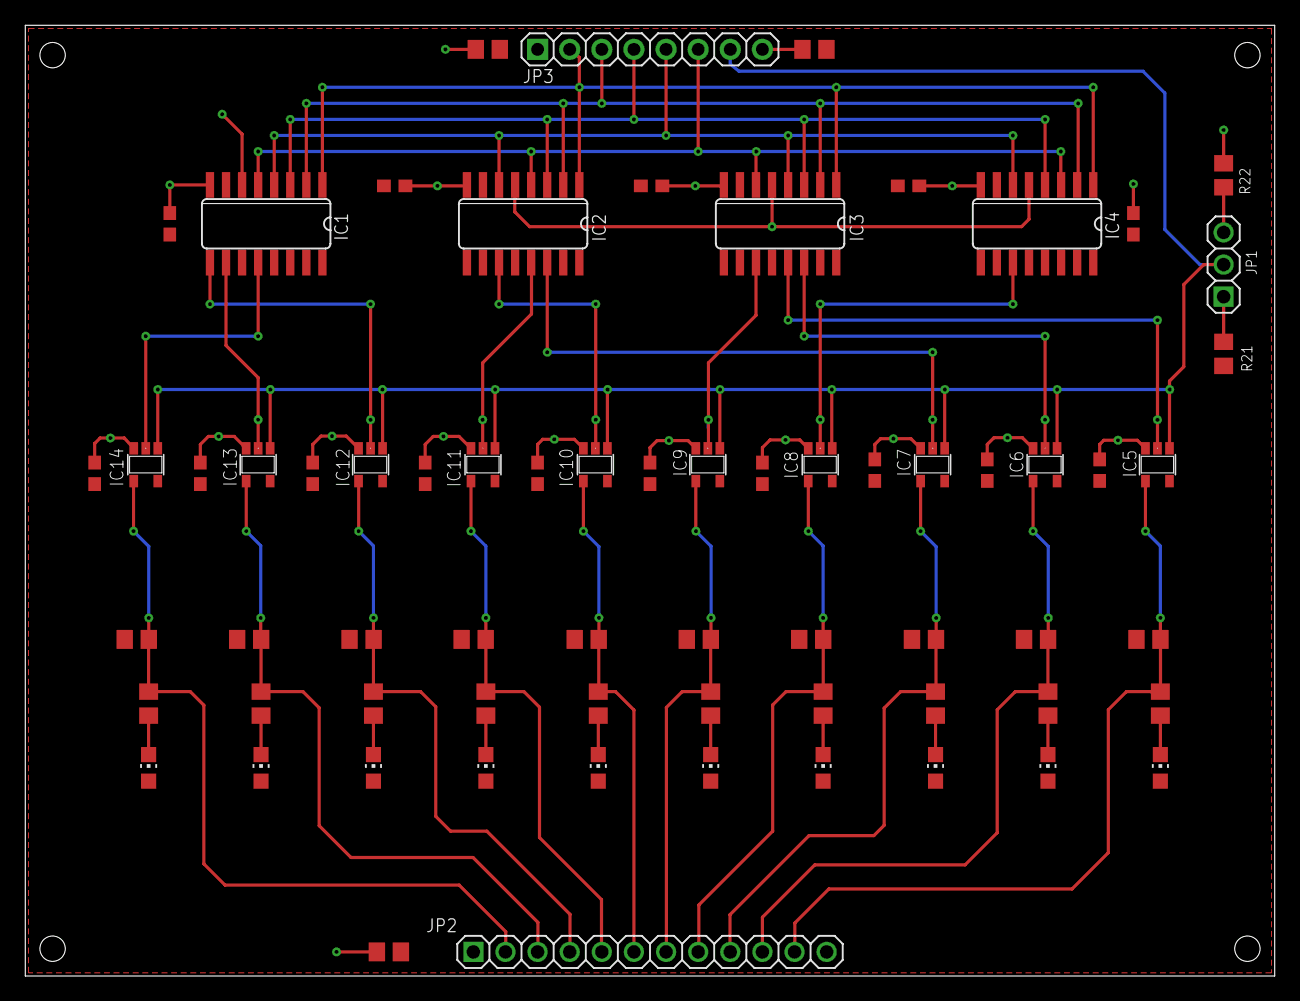
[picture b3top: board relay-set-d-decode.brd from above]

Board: 2 copper layers, 98.8 x 75.2 mm, 67 parts (0 on the bottom side), 40 nets.

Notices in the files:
parts and their libraries:
SparkFun-DiscreteSemi: Licensing: Creative Commons ShareAlike 4.0 International - https://creativecommons.org/licenses/by-sa/4.0
